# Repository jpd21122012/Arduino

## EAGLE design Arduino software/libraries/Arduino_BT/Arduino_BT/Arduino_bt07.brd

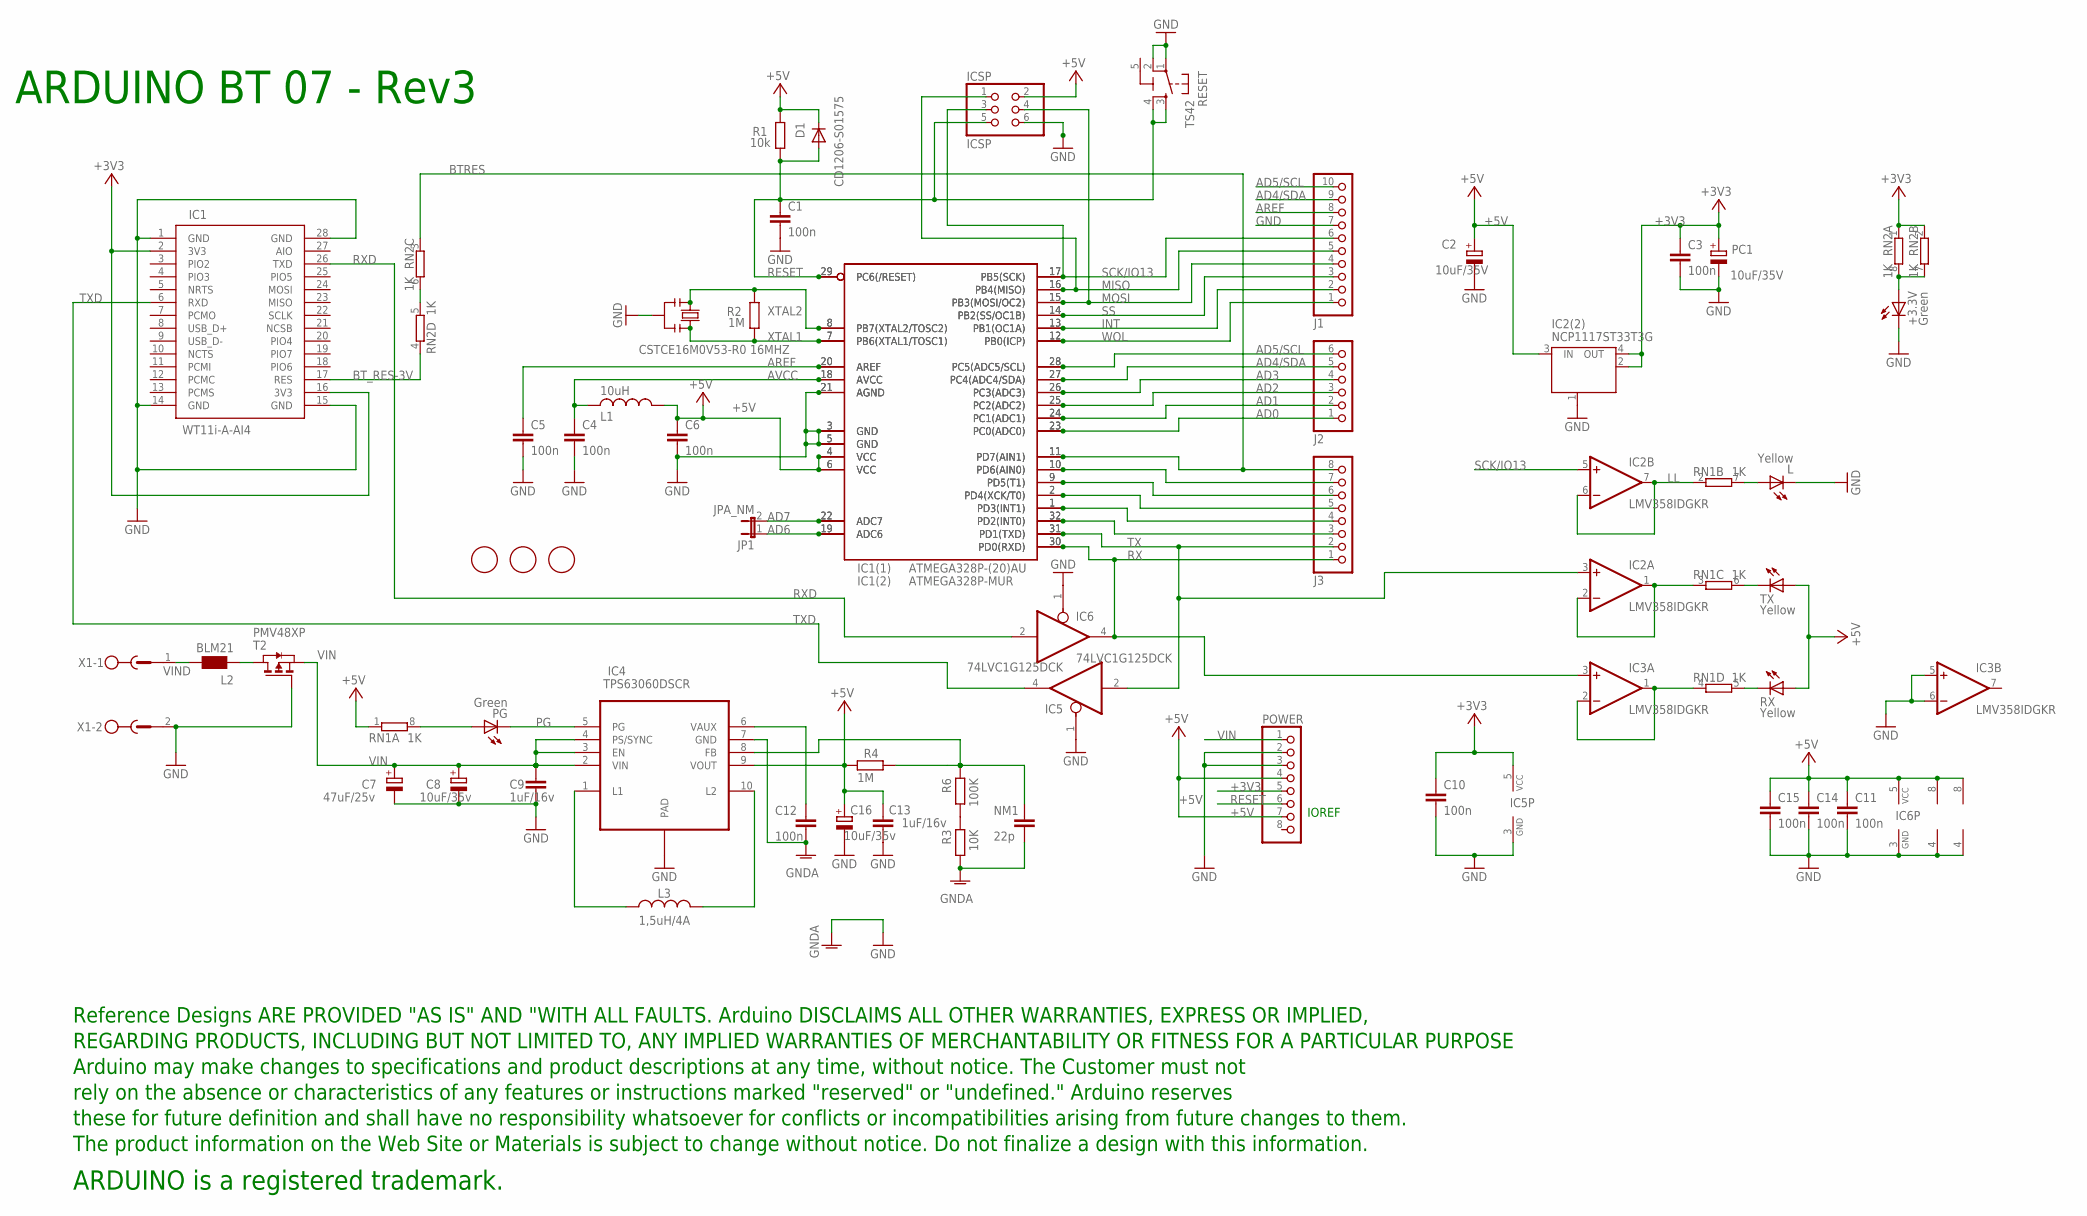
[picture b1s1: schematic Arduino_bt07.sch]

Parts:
+3.3V: Green; CHIPLED_0805
C1, C3, C4, C5, C6, C10, C11, C12, C14, C15: 100n; C0603-ROUND
C2: 10uF/35V; SMC_B
C7: 47uF/25v; PANASONIC_D
C8, C16: 10uF/35v; SMC_B
C9, C13: 1uF/16v; C0603-ROUND
D1: CD1206-S01575; MINIMELF
IC1: WT11i-A-AI4; WT11-A
IC1(1): ATMEGA328P-(20)AU; TQFP32-08
IC1(2): ATMEGA328P-MUR; MLF32
IC2, IC3: LMV358IDGKR; MSOP08
IC2(2): NCP1117ST33T3G; SOT223
IC4: TPS63060DSCR; R-PVSON-10N
IC5, IC6: 74LVC1G125DCK; SC70-5
ICSP: ICSP; 2X03
J1: PINHD-1X10TH; 1X10-TH
J2: PINHD-1X6TH; 1X06-TH
J3: PINHD-1X8TH; 1X08-TH
JP1: JPA_NM; JP1
L: Yellow; CHIPLED_0805
L1: 10uH; L2012C
L2: BLM21; 0805
L3: 1,5uH/4A; SRR0604
NM1: 22p; C0603-ROUND
PC1: 10uF/35V; SMC_B
PG: Green; CHIPLED_0805
POWER: PINHD-1X8TH; 1X08-TH
R1: 10k; R0603-ROUND
R2, R4: 1M; R0603-ROUND
R3: 10K; R0603-ROUND
R6: 100K; R0603-ROUND
RESET: TS42
RN1, RN2: 1K; CAY16
RX: Yellow; CHIPLED_0805
T2: PMV48XP; SOT-23
TX: Yellow; CHIPLED_0805
U$1, U$2, U$3: FIDUCIALMOUNT; FIDUCIA-MOUNT
U$4: DISCLAIMER
X1: MSTBV2
Y1: CSTCE16M0V53-R0 16MHZ; RESONATOR

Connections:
5-GND: RESET.5 (5-GND)
+3V3: C3.1, C10.1, IC1.2 (3V3), IC1.16 (3V3), IC2(2).2 (OUT), IC2(2).4 (OUT), IC5.5 (VCC), PC1.+, POWER.5, RN2.1, RN2.2 (1)
+5V: C2.+, C6.1, C11.1, C13.1, C14.1, C15.1, C16.+, D1.C, IC1(1).4 (VCC), IC1(1).6 (VCC), IC1(2).4 (VCC), IC1(2).6 (VCC), IC2.8 (V+), IC2(2).3 (IN), IC3.8 (V+), IC4.9 (VOUT), IC6.5 (VCC), ICSP.2, L1.1, POWER.4, POWER.7, R1.2, R4.1, RN1.1, RX.A, TX.A
AD0: IC1(1).23 (PC0(ADC0)), IC1(2).23 (PC0(ADC0)), J2.1
AD1: IC1(1).24 (PC1(ADC1)), IC1(2).24 (PC1(ADC1)), J2.2
AD2: IC1(1).25 (PC2(ADC2)), IC1(2).25 (PC2(ADC2)), J2.3
AD3: IC1(1).26 (PC3(ADC3)), IC1(2).26 (PC3(ADC3)), J2.4
AD4/SDA: IC1(1).27 (PC4(ADC4/SDA)), IC1(2).27 (PC4(ADC4/SDA)), J1.9, J2.5
AD5/SCL: IC1(1).28 (PC5(ADC5/SCL)), IC1(2).28 (PC5(ADC5/SCL)), J1.10, J2.6
AD6: IC1(1).19 (ADC6), IC1(2).19 (ADC6), JP1.1
AD7: IC1(1).22 (ADC7), IC1(2).22 (ADC7), JP1.2
AREF: C5.1, IC1(1).20 (AREF), IC1(2).20 (AREF), J1.8
AVCC: C4.1, IC1(1).18 (AVCC), IC1(2).18 (AVCC), L1.2
BTRES: IC1(1).11 (PD7(AIN1)), IC1(2).11 (PD7(AIN1)), J3.8, RN2.3 (1)
BT_RES-3V: IC1.17 (RES), RN2.4 (1)
GND: +3.3V.C, C1.2, C2.-, C3.2, C4.2, C5.2, C6.2, C7.-, C8.-, C9.2, C10.2, C11.2, C13.2, C14.2, C15.2, C16.-, IC1.1 (GND), IC1.14 (GND), IC1.15 (GND), IC1.28 (GND), IC1(1).3 (GND), IC1(1).5 (GND), IC1(1).21 (AGND), IC1(2).3 (GND), IC1(2).5 (GND), IC1(2).21 (AGND), IC2.4 (V-), IC2(2).1 (GND/ADJ), IC3.4 (V-), IC3.5 (+IN), IC3.6 (-IN), IC4.PAD, IC5.1 (OE), IC5.3 (GND), IC6.1 (OE), IC6.3 (GND), ICSP.6, J1.7, L.C, PC1.-, POWER.2, POWER.3, RESET.1, RESET.2, T2.3 (G), X1.2, Y1.2
GNDA: C12.2, IC4.7 (GND), NM1.2, R3.2
INT: IC1(1).13 (PB1(OC1A)), IC1(2).13 (PB1(OC1A)), J1.2
LL: IC2.6 (-IN), IC2.7 (OUT), RN1.2 (1)
MISO: IC1(1).16 (PB4(MISO)), IC1(2).16 (PB4(MISO)), ICSP.1, J1.5
MOSI: IC1(1).15 (PB3(MOSI/OC2)), IC1(2).15 (PB3(MOSI/OC2)), ICSP.4, J1.4
unnamed: R3.1, R6.2
unnamed: L.A, RN1.7 (2)
unnamed: RN1.6 (2), TX.C
unnamed: RN1.5 (2), RX.C
unnamed: +3.3V.A, RN2.7 (2), RN2.8 (2)
unnamed: IC2.1 (OUT), IC2.2 (-IN), RN1.3 (1)
unnamed: PG.A, RN1.8 (2)
unnamed: IC3.1 (OUT), IC3.2 (-IN), RN1.4 (1)
unnamed: L2.1, T2.1 (D)
unnamed: IC1(1).1 (PD3(INT1)), IC1(2).1 (PD3(INT1)), J3.4
unnamed: IC1(1).2 (PD4(XCK/T0)), IC1(2).2 (PD4(XCK/T0)), J3.5
unnamed: IC1(1).9 (PD5(T1)), IC1(2).9 (PD5(T1)), J3.6
unnamed: IC1(1).10 (PD6(AIN0)), IC1(2).10 (PD6(AIN0)), J3.7
unnamed: IC4.10 (L2), L3.P$2 (2)
unnamed: RN2.5 (2), RN2.6 (2)
unnamed: IC1(1).32 (PD2(INT0)), IC1(2).32 (PD2(INT0)), J3.3
unnamed: C12.1, IC4.6 (VAUX)
unnamed: IC4.8 (FB), NM1.1, R4.2, R6.1
unnamed: IC4.1 (L1), L3.P$1 (1)
PG: IC4.5 (PG), PG.C
RESET: C1.1, D1.A, IC1(1).29 (PC6(/RESET)), IC1(2).29 (PC6(/RESET)), ICSP.5, POWER.6, R1.1, RESET.3, RESET.4
RX: IC1(1).30 (PD0(RXD)), IC1(2).30 (PD0(RXD)), IC3.3 (+IN), IC6.4 (O), J3.1
RXD: IC1.26 (TXD), IC6.2 (I)
SCK/IO13: IC1(1).17 (PB5(SCK)), IC1(2).17 (PB5(SCK)), IC2.5 (+IN), ICSP.3, J1.6
SS: IC1(1).14 (PB2(SS/OC1B)), IC1(2).14 (PB2(SS/OC1B)), J1.3
TX: IC1(1).31 (PD1(TXD)), IC1(2).31 (PD1(TXD)), IC2.3 (+IN), IC5.2 (I), J3.2
TXD: IC1.6 (RXD), IC5.4 (O)
VIN: C7.+, C8.+, C9.1, IC4.2 (VIN), IC4.3 (EN), IC4.4 (PS/SYNC), POWER.1, T2.2 (S)
VIND: L2.2, X1.1
WOL: IC1(1).12 (PB0(ICP)), IC1(2).12 (PB0(ICP)), J1.1
XTAL1: IC1(1).7 (PB6(XTAL1/TOSC1)), IC1(2).7 (PB6(XTAL1/TOSC1)), R2.1, Y1.3
XTAL2: IC1(1).8 (PB7(XTAL2/TOSC2)), IC1(2).8 (PB7(XTAL2/TOSC2)), R2.2, Y1.1

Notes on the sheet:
ARDUINO BT 07 - Rev3
IOREF

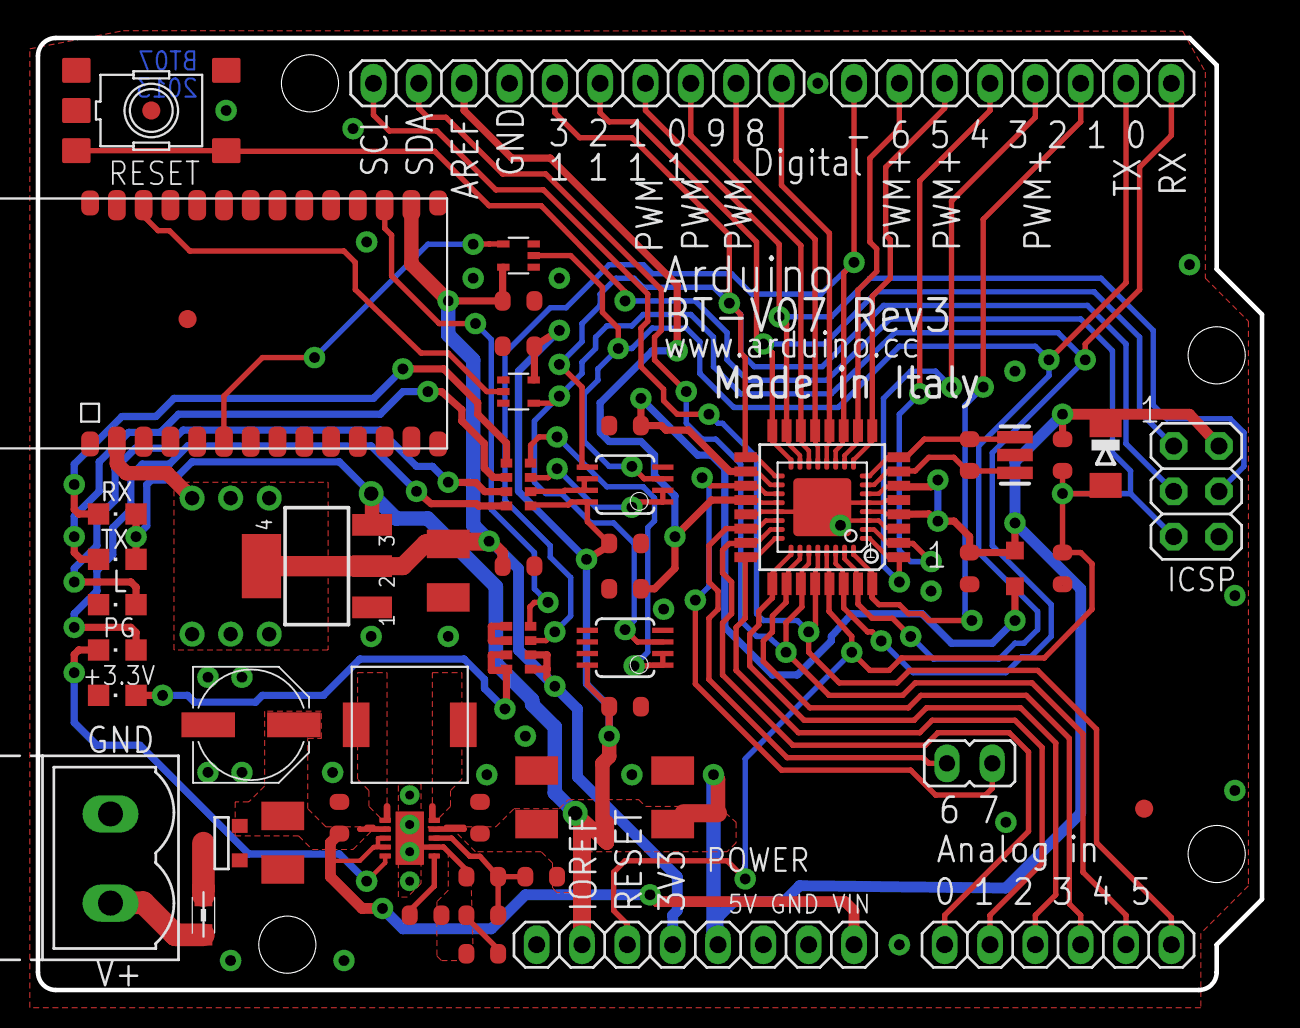
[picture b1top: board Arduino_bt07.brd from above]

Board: 2 copper layers, 68.6 x 53.3 mm, 57 parts (0 on the bottom side), 52 nets.

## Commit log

2017-02-03 :space_invader: Added .gitattributes & .gitignore files
2017-02-04 Use of different libraries and functions in Arduino IDE
